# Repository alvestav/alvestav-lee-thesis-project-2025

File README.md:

# alvestav-lee-thesis-project-2025
 This is the GitHub repository for the bachelor thesis project in KTH computer and electronics engineering

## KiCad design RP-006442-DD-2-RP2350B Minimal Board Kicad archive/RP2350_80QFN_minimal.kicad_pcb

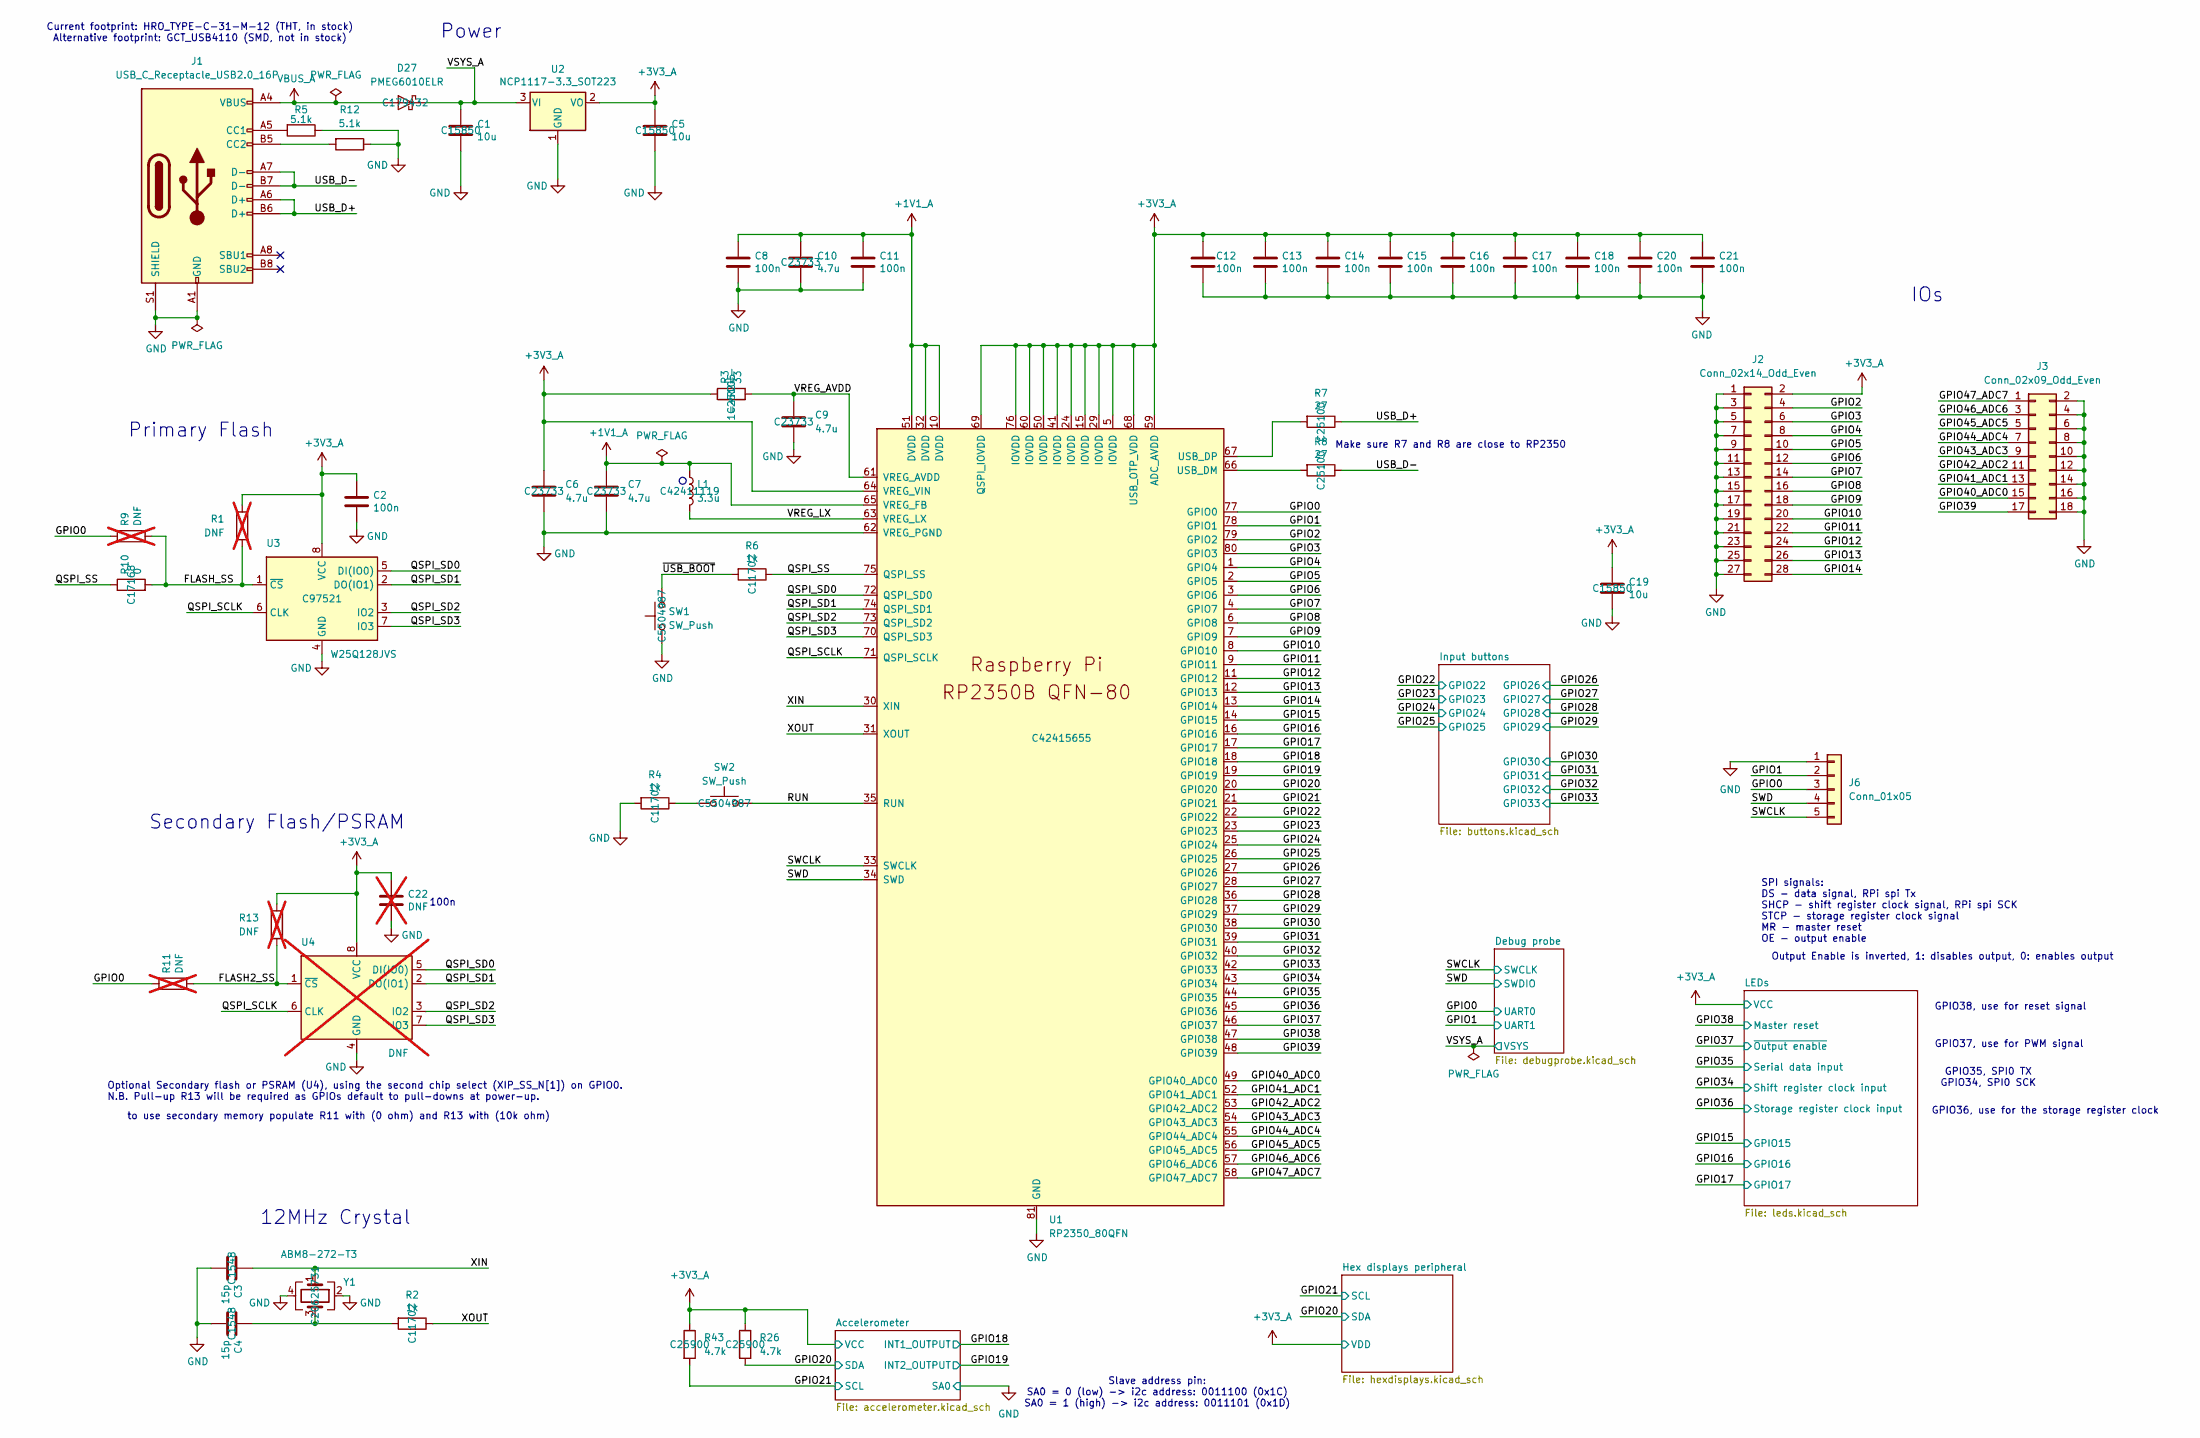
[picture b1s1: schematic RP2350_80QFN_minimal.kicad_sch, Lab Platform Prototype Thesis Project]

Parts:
C1, C5, C19: 10u; C_0805_2012Metric; LCSC C15850
C2, C8, C11, C12, C13, C14, C15, C16, C17, C18, C20, C21: 100n; C_0402_1005Metric; LCSC C1525
C3, C4: 15p; C_0402_1005Metric; LCSC C1548
C6, C7: 4.7u; C_0402_1005Metric_small_pads; LCSC C23733
C9, C10: 4.7u; C_0402_1005Metric; LCSC C23733
C22: DNF; C_0402_1005Metric; not fitted
D27: PMEG6010ELR; Nexperia_CFP3_SOD-123W; LCSC C179432
J1: USB_C_Receptacle_USB2.0_16P; USB_C_Receptacle_HRO_TYPE-C-31-M-12; LCSC C165948
J2: Conn_02x14_Odd_Even; PinHeader_2x14_P2.54mm_Vertical
J3: Conn_02x09_Odd_Even; PinHeader_2x09_P2.54mm_Vertical
J6: Conn_01x05; PinHeader_1x05_P2.54mm_Vertical
L1: 3.3u; L_pol_2016; LCSC C42411119
R1, R9, R11, R13: DNF; R_0402_1005Metric; not fitted
R2, R4, R6: 1k; R_0402_1005Metric; LCSC C11702
R3: 33; R_0402_1005Metric; LCSC C25105
R5, R12: 5.1k; R_0402_1005Metric; LCSC C25905
R7, R8: 27; R_0402_1005Metric; LCSC C25100
R10: 0; R_0402_1005Metric; LCSC C17168
R26, R43: 4.7k; R_0402_1005Metric; LCSC C25900
SW1, SW2: SW_Push; SW_Push_1P1T_NO_Vertical_Wuerth_434133025816; LCSC C5504987
U1: RP2350_80QFN; RP2350-QFN-80-1EP_10x10_P0.4mm_EP3.4x3.4mm_ThermalVias; LCSC C42415655
U2: NCP1117-3.3_SOT223; SOT-223-3_TabPin2; LCSC C26537
U3: W25Q128JVS; SOIC127P790X216-8N; LCSC C97521
U4: DNF; SOIC127P790X216-8N; not fitted
Y1: ABM8-272-T3; Crystal_SMD_3225-4Pin_3.2x2.5mm; LCSC C20625731

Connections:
+1V1_A: C7.1, C8.1, C10.1, C11.1, L1.1, U1.10 (DVDD), U1.32 (DVDD), U1.51 (DVDD), U1.65 (VREG_FB)
+3V3_A: C2.1, C5.1, C6.1, C12.1, C13.1, C14.1, C15.1, C16.1, C17.1, C18.1, C19.1, C20.1, C21.1, C22.1, J2.2, R1.1, R3.1, R13.1, R26.1, R43.1, U1.5 (IOVDD), U1.15 (IOVDD), U1.24 (IOVDD), U1.29 (IOVDD), U1.41 (IOVDD), U1.50 (IOVDD), U1.59 (ADC_AVDD), U1.60 (IOVDD), U1.64 (VREG_VIN), U1.68 (USB_OTP_VDD), U1.69 (QSPI_IOVDD), U1.76 (IOVDD), U2.2 (VO), U3.8 (VCC), U4.8 (VCC); also elsewhere on the board
/FLASH2_SS: R11.2, R13.2, U4.1 (~CS)
/FLASH_SS: R1.2, R9.2, R10.2, U3.1 (~CS)
/GPIO0: J6.3, R9.1, R11.1, U1.77 (GPIO0); also elsewhere on the board
/GPIO1: J6.2, U1.78 (GPIO1); also elsewhere on the board
/GPIO2: J2.4, U1.79 (GPIO2)
/GPIO3: J2.6, U1.80 (GPIO3)
/GPIO4: J2.8, U1.1 (GPIO4)
/GPIO5: J2.10, U1.2 (GPIO5)
/GPIO6: J2.12, U1.3 (GPIO6)
/GPIO7: J2.14, U1.4 (GPIO7)
/GPIO8: J2.16, U1.6 (GPIO8)
/GPIO9: J2.18, U1.7 (GPIO9)
/GPIO10: J2.20, U1.8 (GPIO10)
/GPIO11: J2.22, U1.9 (GPIO11)
/GPIO12: J2.24, U1.11 (GPIO12)
/GPIO13: J2.26, U1.12 (GPIO13)
/GPIO14: J2.28, U1.13 (GPIO14)
/GPIO15: U1.14 (GPIO15); also elsewhere on the board
/GPIO16: U1.16 (GPIO16); also elsewhere on the board
/GPIO17: U1.17 (GPIO17); also elsewhere on the board
/GPIO18: U1.18 (GPIO18); also elsewhere on the board
/GPIO19: U1.19 (GPIO19); also elsewhere on the board
/GPIO20: R26.2, U1.20 (GPIO20); also elsewhere on the board
/GPIO21: R43.2, U1.21 (GPIO21); also elsewhere on the board
/GPIO22: U1.22 (GPIO22); also elsewhere on the board
/GPIO23: U1.23 (GPIO23); also elsewhere on the board
/GPIO24: U1.25 (GPIO24); also elsewhere on the board
/GPIO25: U1.26 (GPIO25); also elsewhere on the board
/GPIO26: U1.27 (GPIO26); also elsewhere on the board
/GPIO27: U1.28 (GPIO27); also elsewhere on the board
/GPIO28: U1.36 (GPIO28); also elsewhere on the board
/GPIO29: U1.37 (GPIO29); also elsewhere on the board
/GPIO30: U1.38 (GPIO30); also elsewhere on the board
/GPIO31: U1.39 (GPIO31); also elsewhere on the board
/GPIO32: U1.40 (GPIO32); also elsewhere on the board
/GPIO33: U1.42 (GPIO33); also elsewhere on the board
/GPIO34: U1.43 (GPIO34); also elsewhere on the board
/GPIO35: U1.44 (GPIO35); also elsewhere on the board
/GPIO36: U1.45 (GPIO36); also elsewhere on the board
/GPIO37: U1.46 (GPIO37); also elsewhere on the board
/GPIO38: U1.47 (GPIO38); also elsewhere on the board
/GPIO39: J3.17, U1.48 (GPIO39)
/GPIO40_ADC0: J3.15, U1.49 (GPIO40_ADC0)
/GPIO41_ADC1: J3.13, U1.52 (GPIO41_ADC1)
/GPIO42_ADC2: J3.11, U1.53 (GPIO42_ADC2)
/GPIO43_ADC3: J3.9, U1.54 (GPIO43_ADC3)
/GPIO44_ADC4: J3.7, U1.55 (GPIO44_ADC4)
/GPIO45_ADC5: J3.5, U1.56 (GPIO45_ADC5)
/GPIO46_ADC6: J3.3, U1.57 (GPIO46_ADC6)
/GPIO47_ADC7: J3.1, U1.58 (GPIO47_ADC7)
/QSPI_SCLK: U1.71 (QSPI_SCLK), U3.6 (CLK), U4.6 (CLK)
/QSPI_SD0: U1.72 (QSPI_SD0), U3.5 (DI(IO0)), U4.5 (DI(IO0))
/QSPI_SD1: U1.74 (QSPI_SD1), U3.2 (DO(IO1)), U4.2 (DO(IO1))
/QSPI_SD2: U1.73 (QSPI_SD2), U3.3 (IO2), U4.3 (IO2)
/QSPI_SD3: U1.70 (QSPI_SD3), U3.7 (IO3), U4.7 (IO3)
/QSPI_SS: R6.1, R10.1, U1.75 (QSPI_SS)
/RUN: SW2.2, U1.35 (RUN)
/SWCLK: J6.5, U1.33 (SWCLK); also elsewhere on the board
/SWD: J6.4, U1.34 (SWD); also elsewhere on the board
/USB_D+: J1.A6 (D+), J1.B6 (D+), R7.1
/USB_D-: J1.A7 (D-), J1.B7 (D-), R8.1
/VREG_AVDD: C9.1, R3.2, U1.61 (VREG_AVDD)
/VREG_LX: L1.2, U1.63 (VREG_LX)
/VSYS_A: C1.1, D27.1 (K), U2.3 (VI); also elsewhere on the board
/XIN: C3.1, U1.30 (XIN), Y1.1
/XOUT: R2.1, U1.31 (XOUT)
/~USB_BOOT: R6.2, SW1.2
GND: C1.2, C2.2, C3.2, C4.2, C5.2, C6.2, C7.2, C8.2, C9.2, C10.2, C11.2, C12.2, C13.2, C14.2, C15.2, C16.2, C17.2, C18.2, C19.2, C20.2, C21.2, C22.2, J1.A1 (GND), J1.A12 (GND), J1.B1 (GND), J1.B12 (GND), J1.S1 (SHIELD), J2.1, J2.3, J2.5, J2.7, J2.9, J2.11, J2.13, J2.15, J2.17, J2.19, J2.21, J2.23, J2.25, J2.27, J3.2, J3.4, J3.6, J3.8, J3.10, J3.12, J3.14, J3.16, J3.18, J6.1, R4.2, R5.1, R12.1, SW1.1, U1.62 (VREG_PGND), U1.81 (GND), U2.1 (GND), U3.4 (GND), U4.4 (GND), Y1.2, Y1.4; also elsewhere on the board
unnamed: C4.1, R2.2, Y1.3
unnamed: J1.A5 (CC1), R5.2
unnamed: J1.B5 (CC2), R12.2
unnamed: R4.1, SW2.1
unnamed: R8.2, U1.66 (USB_DM)
unnamed: R7.2, U1.67 (USB_DP)
VBUS_A: D27.2 (A), J1.A4 (VBUS), J1.A9 (VBUS), J1.B4 (VBUS), J1.B9 (VBUS)

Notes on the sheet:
Optional Secondary flash or PSRAM (U4), using the second chip select (XIP_SS_N[1]) on GPIO0. N.B. Pull-up R13 will be required as GPIOs default to pull-downs at power-up.
IOs
GPIO36, use for the storage register clock
12MHz Crystal
Current footprint: HRO_TYPE-C-31-M-12 (THT, in stock) Alternative footprint: GCT_USB4110 (SMD, not in stock)
GPIO35, SPI0 TX GPIO34, SPI0 SCK
Slave address pin: SA0 = 0 (low) -> i2c address: 0011100 (0x1C) SA0 = 1 (high) -> i2c address: 0011101 (0x1D)
Primary Flash
100n
Make sure R7 and R8 are close to RP2350
Secondary Flash/PSRAM
SPI signals: DS - data signal, RPi spi Tx SHCP - shift register clock signal, RPi spi SCK STCP - storage register clock signal MR - master reset OE - output enable
Output Enable is inverted, 1: disables output, 0: enables output
GPIO37, use for PWM signal
Power
to use secondary memory populate R11 with (0 ohm) and R13 with (10k ohm)
GPIO38, use for reset signal

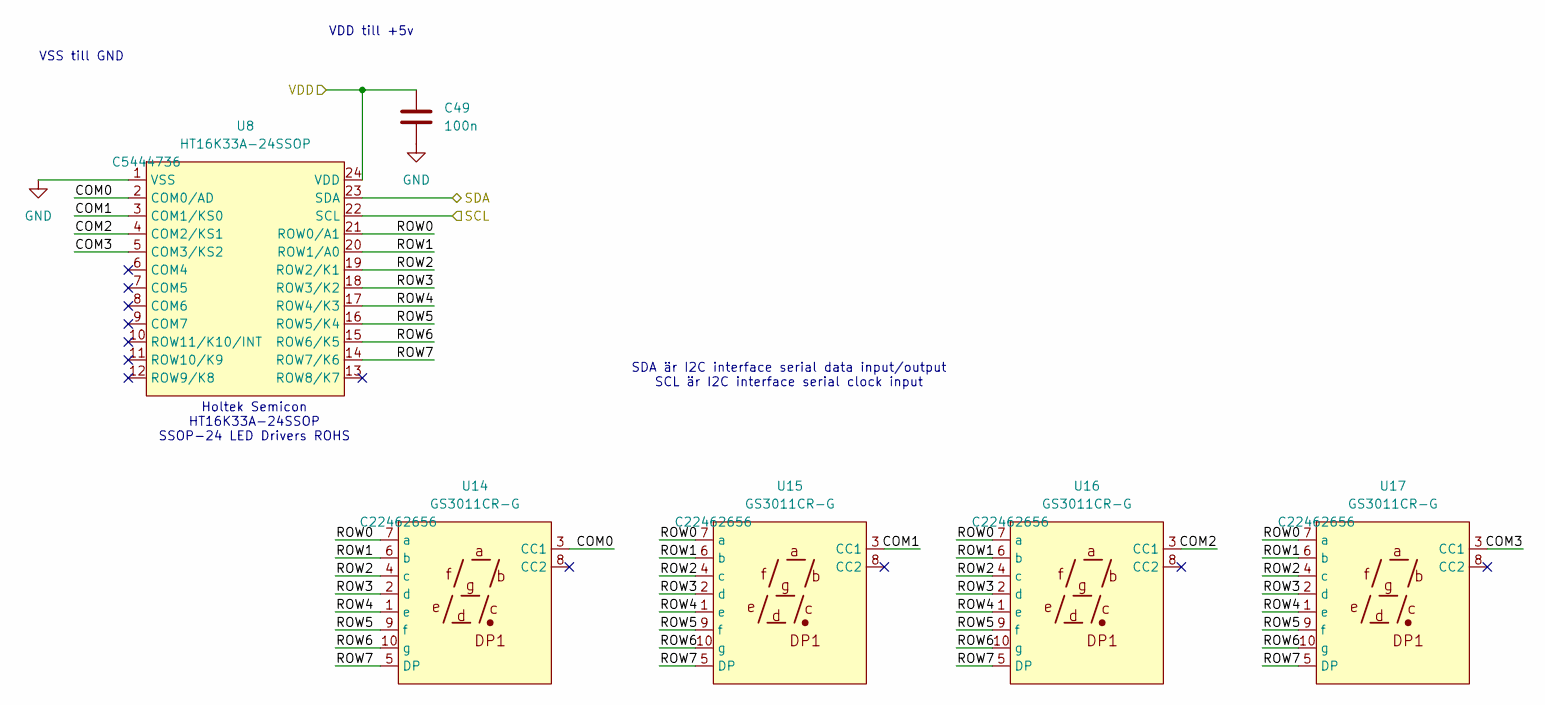
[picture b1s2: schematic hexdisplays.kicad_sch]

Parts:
C49: 100n; C_0402_1005Metric; LCSC C1525
U8: HT16K33A-24SSOP; SSOP-24_3.9x8.7mm_P0.635mm; LCSC C5444736
U14, U15, U16, U17: GS3011CR-G; LCSC C22462656

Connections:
+3V3_A: C49.1, U8.24 (VDD); also elsewhere on the board
/GPIO20: U8.23 (SDA); also elsewhere on the board
/GPIO21: U8.22 (SCL); also elsewhere on the board
/Hex displays peripheral/COM0: U8.2 (COM0/AD), U14.3 (CC1)
/Hex displays peripheral/COM1: U8.3 (COM1/KS0), U15.3 (CC1)
/Hex displays peripheral/COM2: U8.4 (COM2/KS1), U16.3 (CC1)
/Hex displays peripheral/COM3: U8.5 (COM3/KS2), U17.3 (CC1)
/Hex displays peripheral/ROW0: U8.21 (ROW0/A1), U14.7 (a), U15.7 (a), U16.7 (a), U17.7 (a)
/Hex displays peripheral/ROW1: U8.20 (ROW1/A0), U14.6 (b), U15.6 (b), U16.6 (b), U17.6 (b)
/Hex displays peripheral/ROW2: U8.19 (ROW2/K1), U14.4 (c), U15.4 (c), U16.4 (c), U17.4 (c)
/Hex displays peripheral/ROW3: U8.18 (ROW3/K2), U14.2 (d), U15.2 (d), U16.2 (d), U17.2 (d)
/Hex displays peripheral/ROW4: U8.17 (ROW4/K3), U14.1 (e), U15.1 (e), U16.1 (e), U17.1 (e)
/Hex displays peripheral/ROW5: U8.16 (ROW5/K4), U14.9 (f), U15.9 (f), U16.9 (f), U17.9 (f)
/Hex displays peripheral/ROW6: U8.15 (ROW6/K5), U14.10 (g), U15.10 (g), U16.10 (g), U17.10 (g)
/Hex displays peripheral/ROW7: U8.14 (ROW7/K6), U14.5 (DP), U15.5 (DP), U16.5 (DP), U17.5 (DP)
GND: C49.2, U8.1 (VSS); also elsewhere on the board

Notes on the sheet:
SDA är I2C interface serial data input/output SCL är I2C interface serial clock input
VSS till GND
VDD till +5v
Holtek Semicon HT16K33A-24SSOP SSOP-24 LED Drivers ROHS

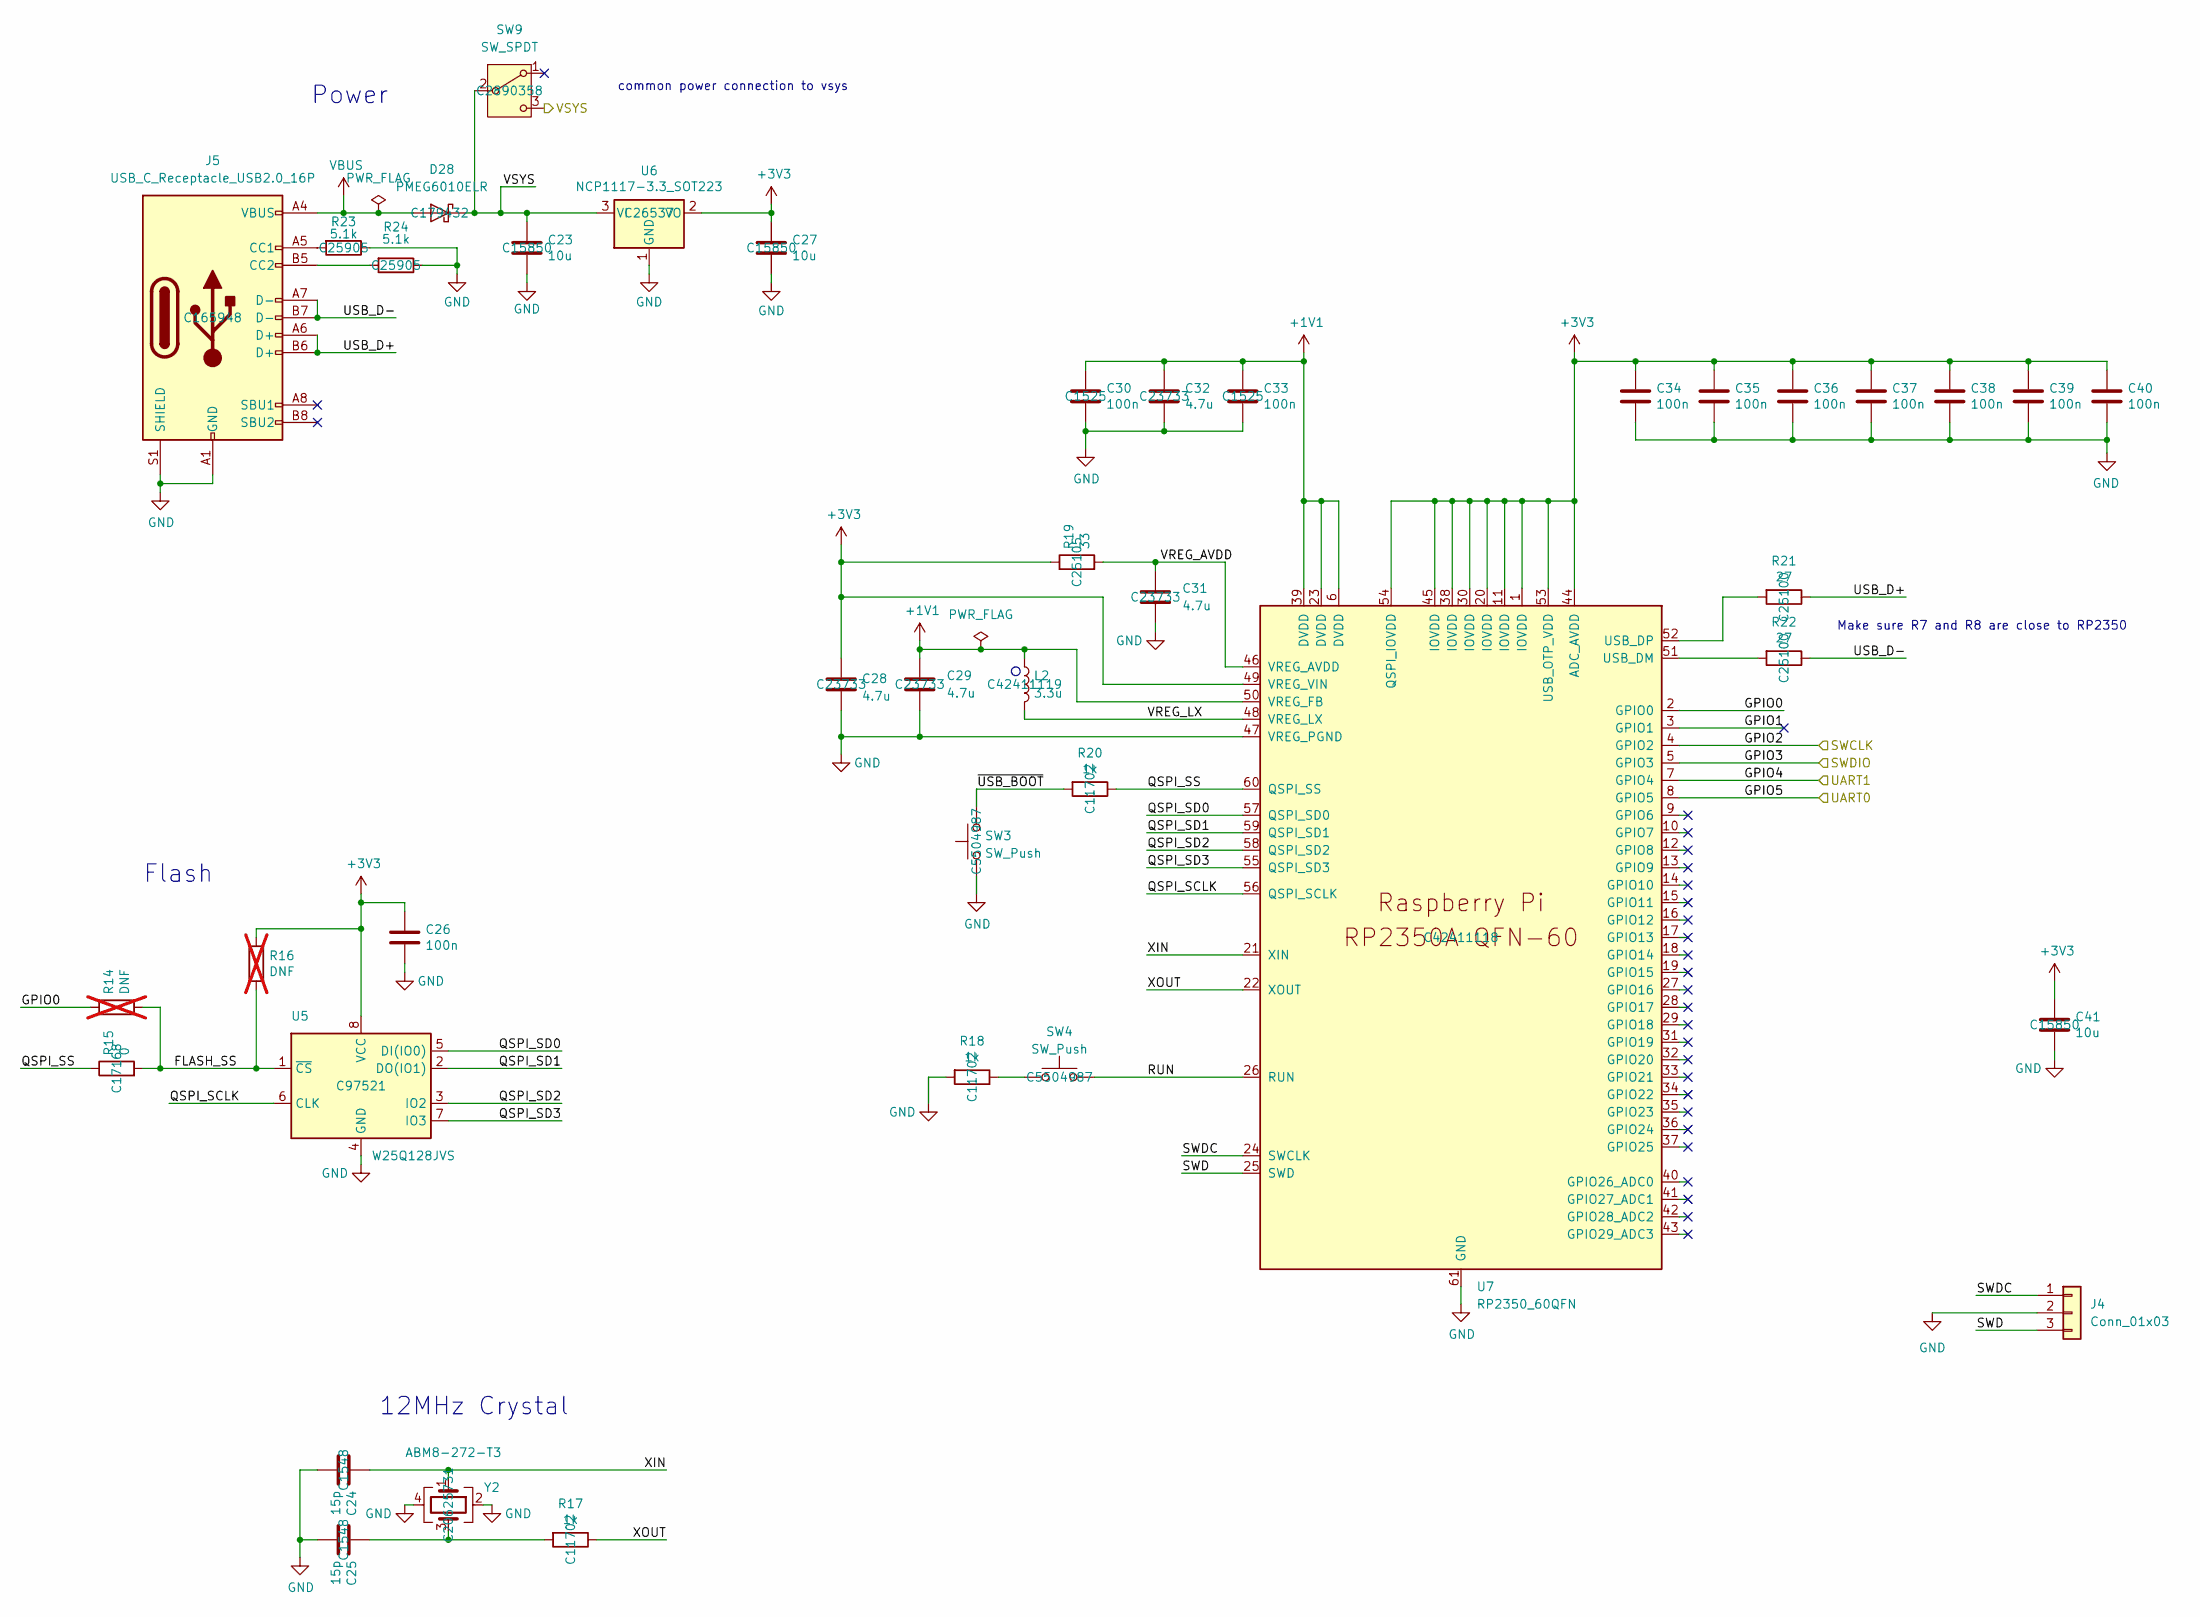
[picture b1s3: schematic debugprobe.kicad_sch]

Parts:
C23, C27, C41: 10u; C_0805_2012Metric; LCSC C15850
C24, C25: 15p; C_0402_1005Metric; LCSC C1548
C26, C30, C33, C34, C35, C36, C37, C38, C39, C40: 100n; C_0402_1005Metric; LCSC C1525
C28, C29: 4.7u; C_0402_1005Metric_small_pads; LCSC C23733
C31, C32: 4.7u; C_0402_1005Metric; LCSC C23733
D28: PMEG6010ELR; Nexperia_CFP3_SOD-123W; LCSC C179432
J4: Conn_01x03; PinHeader_1x03_P2.54mm_Vertical
J5: USB_C_Receptacle_USB2.0_16P; USB_C_Receptacle_HRO_TYPE-C-31-M-12; LCSC C165948
L2: 3.3u; L_pol_2016; LCSC C42411119
R14, R16: DNF; R_0402_1005Metric; not fitted
R15: 0; R_0402_1005Metric; LCSC C17168
R17, R18, R20: 1k; R_0402_1005Metric; LCSC C11702
R19: 33; R_0402_1005Metric; LCSC C25105
R21, R22: 27; R_0402_1005Metric; LCSC C25100
R23, R24: 5.1k; R_0402_1005Metric; LCSC C25905
SW3, SW4: SW_Push; SW_Push_1P1T_NO_Vertical_Wuerth_434133025816; LCSC C5504987
SW9: SW_SPDT; SW_SPDT_G-Switch_MK-12C03-G015; LCSC C2890358
U5: W25Q128JVS; SOIC127P790X216-8N; LCSC C97521
U6: NCP1117-3.3_SOT223; SOT-223-3_TabPin2; LCSC C26537
U7: RP2350_60QFN; RP2350-QFN-60-1EP_7x7_P0.4mm_EP3.4x3.4mm_ThermalVias; LCSC C42411118
Y2: ABM8-272-T3; Crystal_SMD_3225-4Pin_3.2x2.5mm; LCSC C20625731

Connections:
+1V1: C29.1, C30.1, C32.1, C33.1, L2.1, U7.6 (DVDD), U7.23 (DVDD), U7.39 (DVDD), U7.50 (VREG_FB)
+3V3: C26.1, C27.1, C28.1, C34.1, C35.1, C36.1, C37.1, C38.1, C39.1, C40.1, C41.1, R16.1, R19.1, U5.8 (VCC), U6.2 (VO), U7.1 (IOVDD), U7.11 (IOVDD), U7.20 (IOVDD), U7.30 (IOVDD), U7.38 (IOVDD), U7.44 (ADC_AVDD), U7.45 (IOVDD), U7.49 (VREG_VIN), U7.53 (USB_OTP_VDD), U7.54 (QSPI_IOVDD)
/Debug probe/FLASH_SS: R14.2, R15.2, R16.2, U5.1 (~CS)
/Debug probe/GPIO0: R14.1, U7.2 (GPIO0)
/Debug probe/GPIO1: U7.3 (GPIO1)
/Debug probe/QSPI_SCLK: U5.6 (CLK), U7.56 (QSPI_SCLK)
/Debug probe/QSPI_SD0: U5.5 (DI(IO0)), U7.57 (QSPI_SD0)
/Debug probe/QSPI_SD1: U5.2 (DO(IO1)), U7.59 (QSPI_SD1)
/Debug probe/QSPI_SD2: U5.3 (IO2), U7.58 (QSPI_SD2)
/Debug probe/QSPI_SD3: U5.7 (IO3), U7.55 (QSPI_SD3)
/Debug probe/QSPI_SS: R15.1, R20.1, U7.60 (QSPI_SS)
/Debug probe/RUN: SW4.2, U7.26 (RUN)
/Debug probe/SWD: J4.3, U7.25 (SWD)
/Debug probe/SWDC: J4.1, U7.24 (SWCLK)
/Debug probe/USB_D+: J5.A6 (D+), J5.B6 (D+), R21.1
/Debug probe/USB_D-: J5.A7 (D-), J5.B7 (D-), R22.1
/Debug probe/VREG_AVDD: C31.1, R19.2, U7.46 (VREG_AVDD)
/Debug probe/VREG_LX: L2.2, U7.48 (VREG_LX)
/Debug probe/XIN: C24.1, U7.21 (XIN), Y2.1
/Debug probe/XOUT: R17.1, U7.22 (XOUT)
/Debug probe/~USB_BOOT: R20.2, SW3.2
/GPIO0: U7.8 (GPIO5); also elsewhere on the board
/GPIO1: U7.7 (GPIO4); also elsewhere on the board
/SWCLK: U7.4 (GPIO2); also elsewhere on the board
/SWD: U7.5 (GPIO3); also elsewhere on the board
/VSYS_A: C23.1, D28.1 (K), SW9.2 (B), SW9.3 (C), U6.3 (VI); also elsewhere on the board
GND: C23.2, C24.2, C25.2, C26.2, C27.2, C28.2, C29.2, C30.2, C31.2, C32.2, C33.2, C34.2, C35.2, C36.2, C37.2, C38.2, C39.2, C40.2, C41.2, J4.2, J5.A1 (GND), J5.A12 (GND), J5.B1 (GND), J5.B12 (GND), J5.S1 (SHIELD), R18.2, R23.1, R24.1, SW3.1, U5.4 (GND), U6.1 (GND), U7.47 (VREG_PGND), U7.61 (GND), Y2.2, Y2.4; also elsewhere on the board
unnamed: C25.1, R17.2, Y2.3
unnamed: J5.A5 (CC1), R23.2
unnamed: J5.B5 (CC2), R24.2
unnamed: R18.1, SW4.1
unnamed: R22.2, U7.51 (USB_DM)
unnamed: R21.2, U7.52 (USB_DP)
VBUS: D28.2 (A), J5.A4 (VBUS), J5.A9 (VBUS), J5.B4 (VBUS), J5.B9 (VBUS)

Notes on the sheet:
Power
Flash
common power connection to vsys
Make sure R7 and R8 are close to RP2350
12MHz Crystal

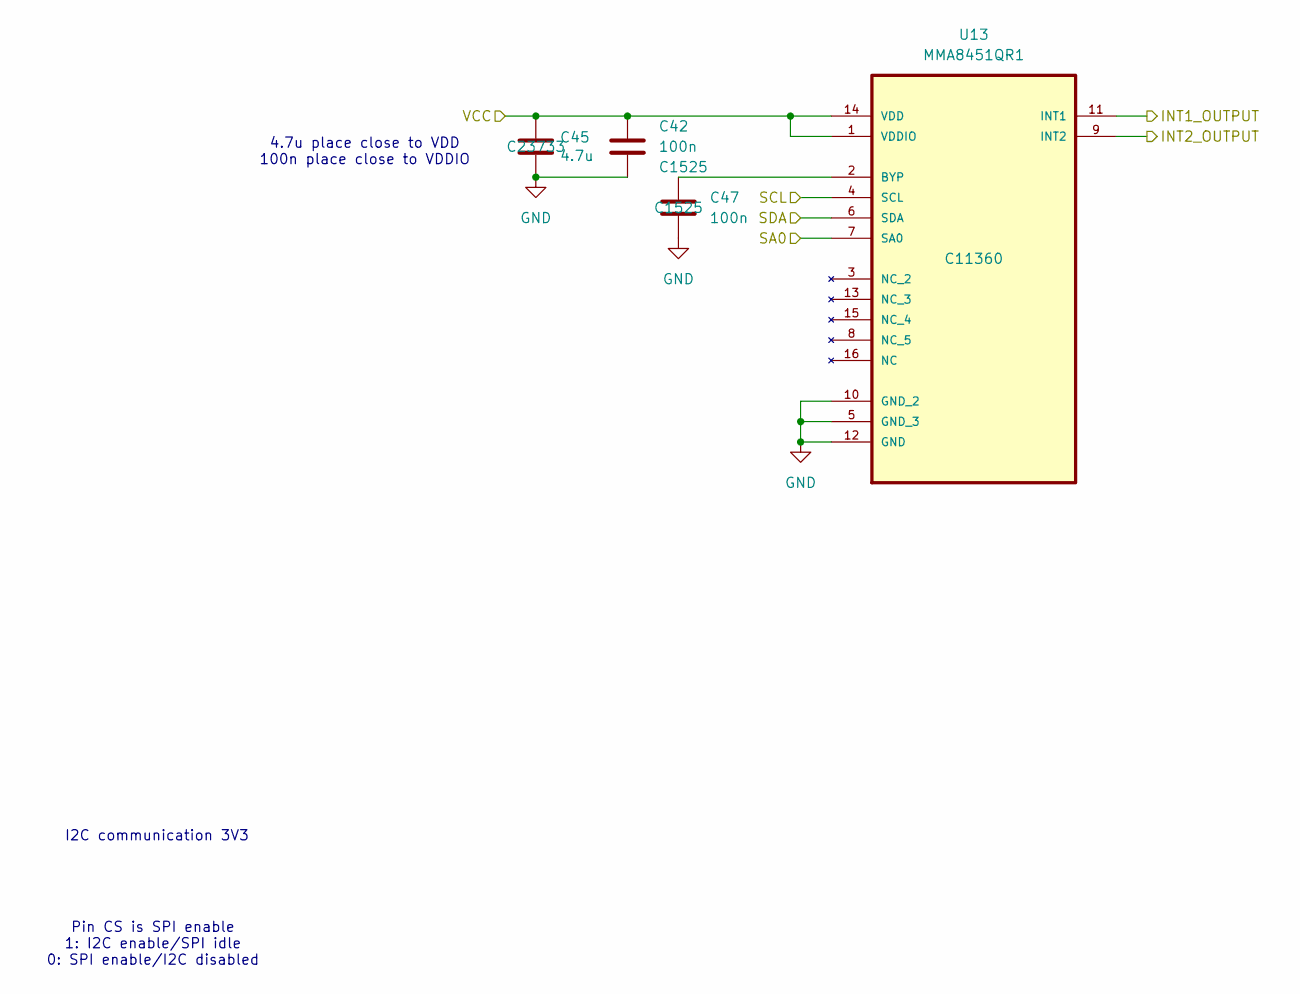
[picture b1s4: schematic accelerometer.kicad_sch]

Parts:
C42, C47: 100n; C_0402_1005Metric; LCSC C1525
C45: 4.7u; C_0402_1005Metric; LCSC C23733
U13: MMA8451QR1; QFN50P300X300X100-16N; MPN MMA8451QR1; LCSC C11360

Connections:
+3V3_A: C42.1, C45.1, U13.1 (VDDIO), U13.14 (VDD); also elsewhere on the board
/GPIO18: U13.11 (INT1); also elsewhere on the board
/GPIO19: U13.9 (INT2); also elsewhere on the board
/GPIO20: U13.6 (SDA); also elsewhere on the board
/GPIO21: U13.4 (SCL); also elsewhere on the board
GND: C42.2, C45.2, C47.2, U13.5 (GND_3), U13.7 (SA0), U13.10 (GND_2), U13.12 (GND); also elsewhere on the board
unnamed: C47.1, U13.2 (BYP)

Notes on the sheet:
4.7u place close to VDD 100n place close to VDDIO
Pin CS is SPI enable 1: I2C enable/SPI idle 0: SPI enable/I2C disabled
I2C communication 3V3

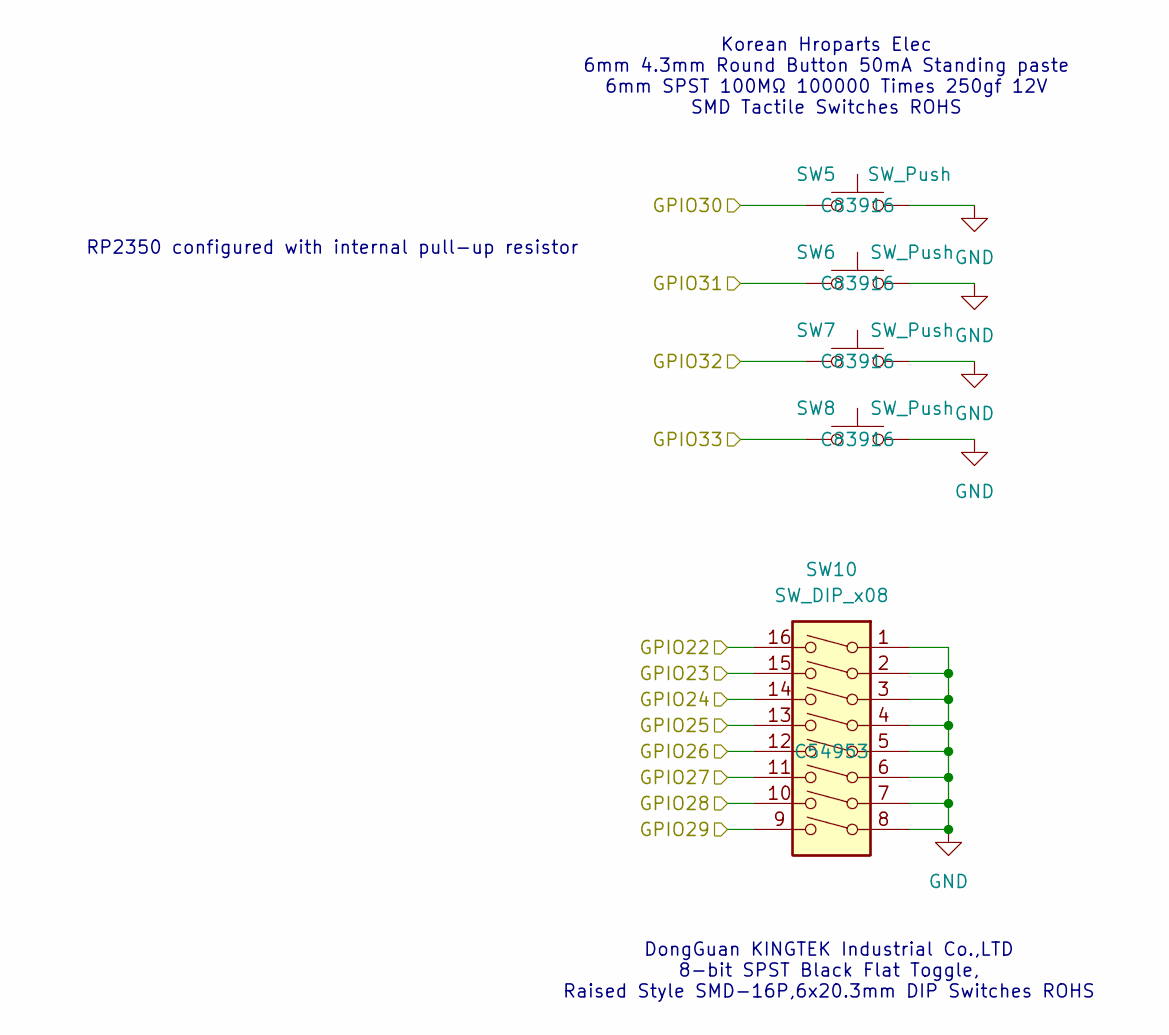
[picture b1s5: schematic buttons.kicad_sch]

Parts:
SW5, SW6, SW7, SW8: SW_Push; SW_Push_K2-1102SP-A4SC-04; LCSC C83916
SW10: SW_DIP_x08; SW_DIP_SPSTx08_Slide_9.78x22.5mm_W8.61mm_P2.54mm; LCSC C54953

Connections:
/GPIO22: SW10.16; also elsewhere on the board
/GPIO23: SW10.15; also elsewhere on the board
/GPIO24: SW10.14; also elsewhere on the board
/GPIO25: SW10.13; also elsewhere on the board
/GPIO26: SW10.12; also elsewhere on the board
/GPIO27: SW10.11; also elsewhere on the board
/GPIO28: SW10.10; also elsewhere on the board
/GPIO29: SW10.9; also elsewhere on the board
/GPIO30: SW5.1; also elsewhere on the board
/GPIO31: SW6.1; also elsewhere on the board
/GPIO32: SW7.1; also elsewhere on the board
/GPIO33: SW8.1; also elsewhere on the board
GND: SW5.2, SW6.2, SW7.2, SW8.2, SW10.1, SW10.2, SW10.3, SW10.4, SW10.5, SW10.6, SW10.7, SW10.8; also elsewhere on the board

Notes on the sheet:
DongGuan KINGTEK Industrial Co.,LTD 8-bit SPST Black Flat Toggle, Raised Style SMD-16P,6x20.3mm DIP Switches ROHS
Korean Hroparts Elec 6mm 4.3mm Round Button 50mA Standing paste 6mm SPST 100MΩ 100000 Times 250gf 12V SMD Tactile Switches ROHS
RP2350 configured with internal pull-up resistor

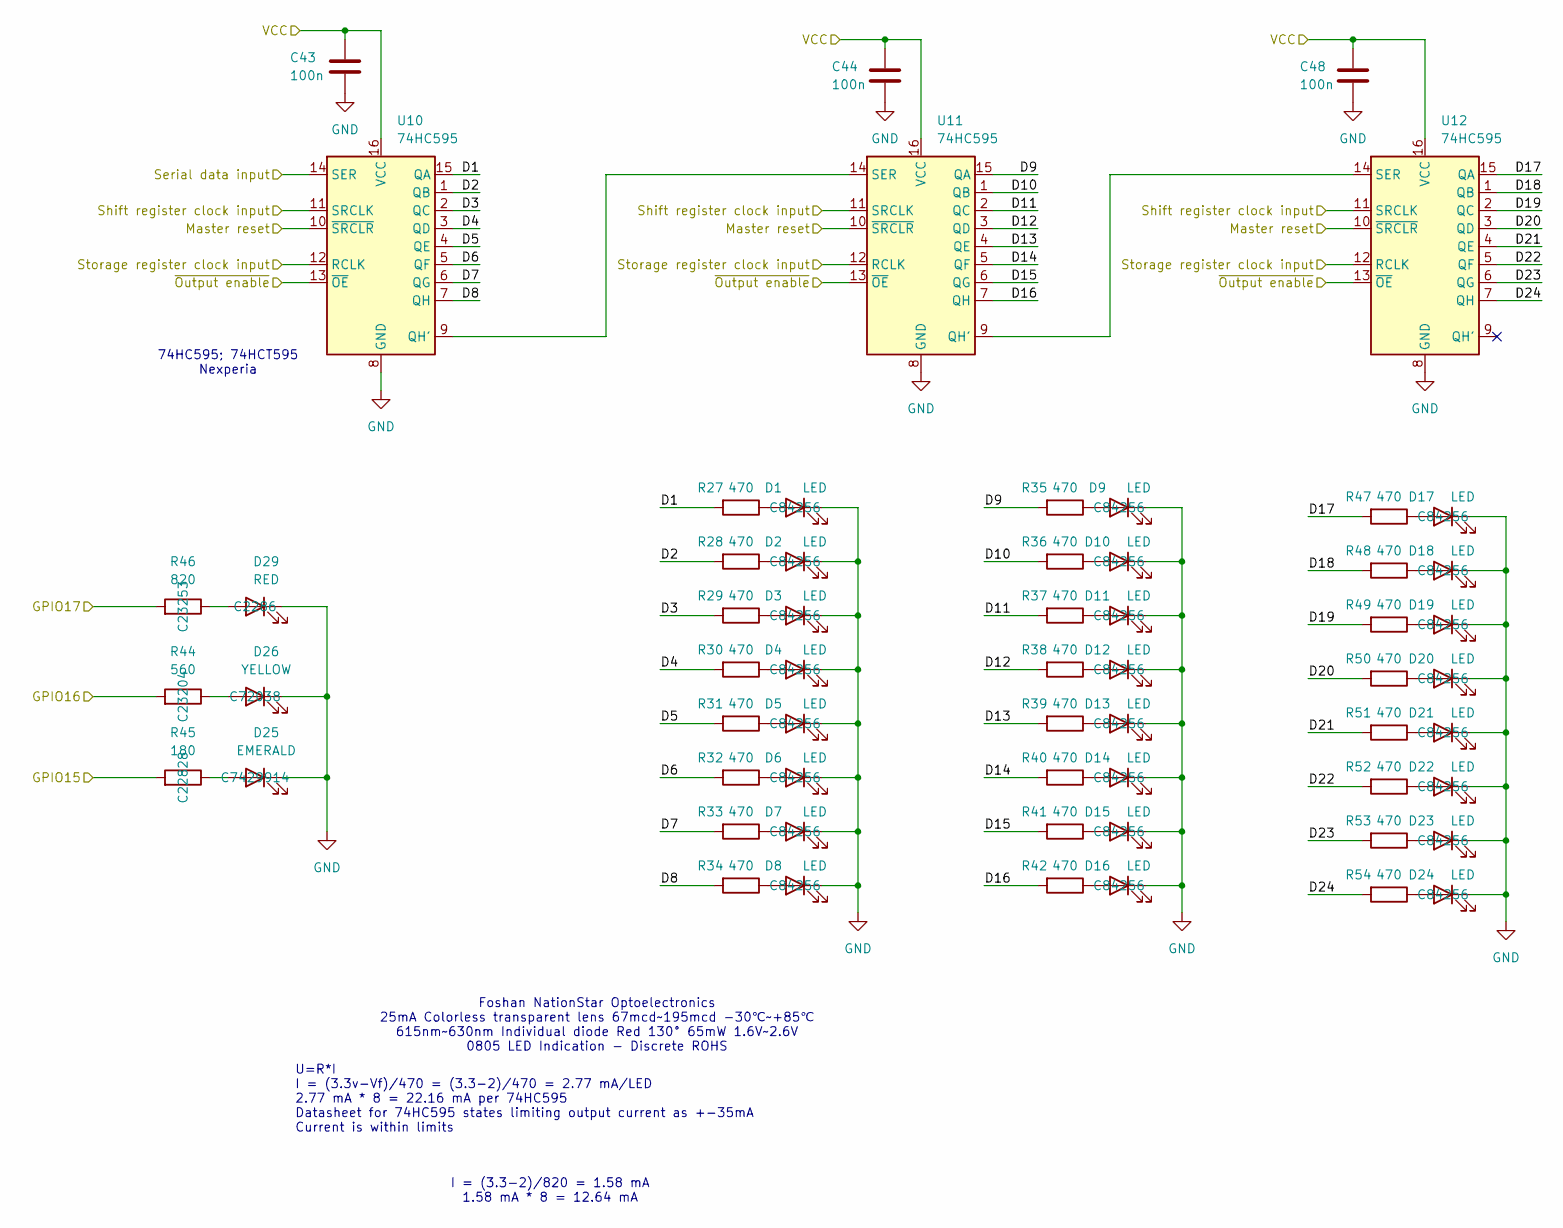
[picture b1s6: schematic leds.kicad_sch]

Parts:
C43, C44, C48: 100n; C_0402_1005Metric; LCSC C1525
D1, D2, D3, D4, D5, D6, D7, D8, D9, D10, D11, D12, D13, D14, D15, D16, D17, D18, D19, D20, D21, D22, D23, D24: LED; LED_0805_2012Metric; LCSC C84256
D25: EMERALD; LED_0603_1608Metric; LCSC C7429914
D26: YELLOW; LED_0603_1608Metric; LCSC C72038
D29: RED; LED_0603_1608Metric; LCSC C2286
R27, R28, R29, R30, R31, R32, R33, R34, R35, R36, R37, R38, R39, R40, R41, R42, R47, R48, R49, R50, R51, R52, R53, R54: 470; R_0402_1005Metric; LCSC C25117
R44: 560; R_0603_1608Metric; LCSC C23204
R45: 180; R_0603_1608Metric; LCSC C22828
R46: 820; R_0603_1608Metric; LCSC C23253
U10, U11, U12: 74HC595; SOIC-16_3.9x9.9mm_P1.27mm; LCSC C5947

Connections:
+3V3_A: C43.1, C44.1, C48.1, U10.16 (VCC), U11.16 (VCC), U12.16 (VCC); also elsewhere on the board
/GPIO15: R45.2; also elsewhere on the board
/GPIO16: R44.2; also elsewhere on the board
/GPIO17: R46.2; also elsewhere on the board
/GPIO34: U10.11 (SRCLK), U11.11 (SRCLK), U12.11 (SRCLK); also elsewhere on the board
/GPIO35: U10.14 (SER); also elsewhere on the board
/GPIO36: U10.12 (RCLK), U11.12 (RCLK), U12.12 (RCLK); also elsewhere on the board
/GPIO37: U10.13 (~OE), U11.13 (~OE), U12.13 (~OE); also elsewhere on the board
/GPIO38: U10.10 (~SRCLR), U11.10 (~SRCLR), U12.10 (~SRCLR); also elsewhere on the board
/LEDs/D1: R27.2, U10.15 (QA)
/LEDs/D2: R28.2, U10.1 (QB)
/LEDs/D3: R29.2, U10.2 (QC)
/LEDs/D4: R30.2, U10.3 (QD)
/LEDs/D5: R31.2, U10.4 (QE)
/LEDs/D6: R32.2, U10.5 (QF)
/LEDs/D7: R33.2, U10.6 (QG)
/LEDs/D8: R34.2, U10.7 (QH)
/LEDs/D9: R35.2, U11.15 (QA)
/LEDs/D10: R36.2, U11.1 (QB)
/LEDs/D11: R37.2, U11.2 (QC)
/LEDs/D12: R38.2, U11.3 (QD)
/LEDs/D13: R39.2, U11.4 (QE)
/LEDs/D14: R40.2, U11.5 (QF)
/LEDs/D15: R41.2, U11.6 (QG)
/LEDs/D16: R42.2, U11.7 (QH)
/LEDs/D17: R47.2, U12.15 (QA)
/LEDs/D18: R48.2, U12.1 (QB)
/LEDs/D19: R49.2, U12.2 (QC)
/LEDs/D20: R50.2, U12.3 (QD)
/LEDs/D21: R51.2, U12.4 (QE)
/LEDs/D22: R52.2, U12.5 (QF)
/LEDs/D23: R53.2, U12.6 (QG)
/LEDs/D24: R54.2, U12.7 (QH)
GND: C43.2, C44.2, C48.2, D1.1 (K), D2.1 (K), D3.1 (K), D4.1 (K), D5.1 (K), D6.1 (K), D7.1 (K), D8.1 (K), D9.1 (K), D10.1 (K), D11.1 (K), D12.1 (K), D13.1 (K), D14.1 (K), D15.1 (K), D16.1 (K), D17.1 (K), D18.1 (K), D19.1 (K), D20.1 (K), D21.1 (K), D22.1 (K), D23.1 (K), D24.1 (K), D25.1 (K), D26.1 (K), D29.1 (K), U10.8 (GND), U11.8 (GND), U12.8 (GND); also elsewhere on the board
unnamed: D1.2 (A), R27.1
unnamed: D2.2 (A), R28.1
unnamed: D3.2 (A), R29.1
unnamed: D4.2 (A), R30.1
unnamed: D5.2 (A), R31.1
unnamed: D6.2 (A), R32.1
unnamed: D7.2 (A), R33.1
unnamed: D8.2 (A), R34.1
unnamed: D9.2 (A), R35.1
unnamed: D10.2 (A), R36.1
unnamed: D11.2 (A), R37.1
unnamed: D12.2 (A), R38.1
unnamed: D13.2 (A), R39.1
unnamed: D14.2 (A), R40.1
unnamed: D15.2 (A), R41.1
unnamed: D16.2 (A), R42.1
unnamed: D17.2 (A), R47.1
unnamed: D18.2 (A), R48.1
unnamed: D19.2 (A), R49.1
unnamed: D20.2 (A), R50.1
unnamed: D21.2 (A), R51.1
unnamed: D22.2 (A), R52.1
unnamed: D23.2 (A), R53.1
unnamed: D24.2 (A), R54.1
unnamed: D25.2 (A), R45.1
unnamed: D26.2 (A), R44.1
unnamed: D29.2 (A), R46.1
unnamed: U10.9 (QH'), U11.14 (SER)
unnamed: U11.9 (QH'), U12.14 (SER)

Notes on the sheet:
74HC595; 74HCT595 Nexperia
I = (3.3-2)/820 = 1.58 mA 1.58 mA * 8 = 12.64 mA
Foshan NationStar Optoelectronics 25mA Colorless transparent lens 67mcd~195mcd -30℃~+85℃ 615nm~630nm Individual diode Red 130° 65mW 1.6V~2.6V 0805 LED Indication - Discrete ROHS
U=R*I I = (3.3v-Vf)/470 = (3.3-2)/470 = 2.77 mA/LED 2.77 mA * 8 = 22.16 mA per 74HC595 Datasheet for 74HC595 states limiting output current as +-35mA Current is within limits
